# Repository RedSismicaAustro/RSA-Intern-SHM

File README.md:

# RSA Intern SHM

Repositorio para la **migración de proyectos electrónicos desde Altium Designer hacia KiCad 10** desarrollados para el sistema **RSA Structural Health Monitoring (SHM)**.

El propósito de este repositorio es preservar los diseños electrónicos existentes, reemplazar las bibliotecas propietarias utilizadas en Altium por bibliotecas locales compatibles con KiCad y establecer un flujo de trabajo estandarizado para el mantenimiento del hardware mediante herramientas de código abierto.

Como parte del proceso de migración, cada proyecto es revisado para verificar la integridad del esquemático y del PCB, actualizar las bibliotecas de símbolos y huellas, asociar modelos tridimensionales, asignar códigos **LCSC** a los componentes compatibles con **JLCPCB** y generar nuevamente todos los archivos necesarios para fabricación y ensamblaje automático.

La documentación específica de cada tarjeta se encuentra en la carpeta **Docs**, mientras que las bibliotecas compartidas se almacenan dentro de **KiCad/libs**, permitiendo reutilizar componentes entre diferentes proyectos y garantizando que cualquier desarrollador pueda abrir los diseños sin depender de configuraciones locales.

---

# Objetivos

El proceso de migración busca establecer una metodología uniforme para todos los proyectos electrónicos del sistema SHM. Los principales objetivos del repositorio son:

- Migrar los diseños electrónicos desde Altium Designer hacia KiCad 10.
- Eliminar dependencias de bibliotecas propietarias.
- Centralizar símbolos, footprints y modelos 3D en bibliotecas locales.
- Mantener todos los proyectos bajo control de versiones mediante Git.
- Preparar los diseños para fabricación y ensamblaje mediante JLCPCB.
- Documentar el proceso de migración para facilitar futuras modificaciones y revisiones.

---

# Estructura del repositorio

El repositorio se organiza de manera que cada proyecto conserve su propia documentación, mientras que las bibliotecas compartidas permanecen centralizadas para facilitar su reutilización.

```text
RSA-Intern-SHM/
│
├── Docs/
│   ├── Nodo/
│   │   └── README.md
│   ├── Concentrador/
│   │   └── README.md
│   ├── Concentrador2/
│   │   └── README.md
│   └── ...
│
├── KiCad/
│   ├── libs/
│   │   ├── RSA.kicad_sym
│   │   ├── RSA.pretty/
│   │   ├── LibExt.pretty/
│   │   └── packages3d/
│   │
│   └── projects/
│       ├── Nodo/
│       ├── Concentrador/
│       ├── Concentrador2/
│       └── ...
│
├── Firmware/
│
├── Production/
│
└── README.md
```

La carpeta `KiCad/projects` contiene los proyectos electrónicos migrados, mientras que `KiCad/libs` almacena todas las bibliotecas compartidas utilizadas por los diferentes diseños. Esta organización evita duplicar componentes y simplifica el mantenimiento de las bibliotecas a medida que nuevos proyectos son incorporados al repositorio.

---

# Herramientas utilizadas

La migración y mantenimiento de los proyectos se realiza utilizando herramientas de código abierto y utilidades complementarias para automatizar la generación de bibliotecas y archivos de fabricación.

| Herramienta | Descripción |
|-------------|-------------|
| KiCad 10 | Diseño y edición de esquemáticos y PCB |
| Python 3 | Automatización de herramientas auxiliares |
| Git | Control de versiones |
| JLC2KiCadLib | Descarga automática de símbolos, footprints y modelos 3D |
| Fabrication Toolkit | Generación de BOM, CPL, Gerbers y NC Drill |
| JLCPCB | Fabricación y ensamblaje PCBA |

---

# Flujo de migración

Todos los proyectos contenidos en este repositorio siguen un procedimiento de migración común con el objetivo de mantener una estructura uniforme y facilitar el mantenimiento futuro.

El proceso comienza con la importación del proyecto desde Altium Designer hacia KiCad. Posteriormente se realiza una revisión completa del esquemático y del PCB para verificar que las conexiones eléctricas, las referencias de componentes y las reglas de diseño hayan sido importadas correctamente.

Una vez validado el diseño, se sustituyen las bibliotecas originales por bibliotecas locales compatibles con KiCad. Cada símbolo queda asociado con su respectiva huella y, cuando está disponible, con su modelo tridimensional.

Posteriormente se revisan los componentes para identificar aquellos compatibles con el servicio PCBA de JLCPCB. A estos componentes se les asigna su correspondiente código LCSC, permitiendo automatizar la generación de la lista de materiales y del archivo de posicionamiento durante el proceso de fabricación.

Finalmente se ejecutan las verificaciones ERC y DRC, se generan los archivos Gerber, NC Drill, BOM y CPL mediante Fabrication Toolkit y se valida la documentación obtenida utilizando el visor de JLCPCB.

---

# Organización de bibliotecas

Uno de los principales objetivos de la migración consiste en eliminar la dependencia de bibliotecas instaladas globalmente. Para ello, todos los símbolos, footprints y modelos tridimensionales utilizados por los proyectos se almacenan dentro del repositorio.

Las bibliotecas principales utilizadas son:

- RSA.kicad_sym
- RSA.pretty
- LibExt.pretty

Los modelos tridimensionales asociados a cada componente se almacenan dentro de la carpeta `packages3d`, mientras que los componentes descargados automáticamente desde JLCPCB se incorporan a las bibliotecas locales mediante **JLC2KiCadLib**.

Esta organización garantiza que cualquier proyecto pueda abrirse correctamente después de clonar el repositorio, independientemente del equipo utilizado.

---

# Proyectos

Actualmente el repositorio contiene varias tarjetas electrónicas migradas desde Altium Designer hacia KiCad 10.

| Proyecto | Descripción |
|-----------|-------------|
| Nodo | Nodo de adquisición de datos del sistema SHM. |
| Concentrador | Tarjeta concentradora de comunicaciones. |
| Concentrador2 | Segunda revisión del concentrador con mejoras de hardware. |

Cada proyecto dispone de un archivo `README.md` independiente dentro de la carpeta `Docs`, donde se documenta el procedimiento de migración, la configuración de bibliotecas, la lista de componentes, los códigos LCSC y el proceso de generación de archivos de fabricación.

---

# Preparación para fabricación

Todos los diseños fueron preparados para ser fabricados utilizando el servicio **JLCPCB PCBA**. Los componentes compatibles emplean códigos **LCSC**, permitiendo automatizar la generación de la lista de materiales y el posicionamiento de componentes durante el ensamblaje.

Antes de generar los archivos de producción se revisan las propiedades de cada componente para configurar correctamente las opciones **Exclude from BOM** y **Exclude from Board**, evitando que conectores, elementos mecánicos o componentes de montaje manual sean incluidos en los archivos de ensamblaje.

La documentación de fabricación generada para cada proyecto incluye:

- Gerber
- NC Drill
- Bill of Materials (BOM)
- Component Placement List (CPL)

Estos archivos pueden almacenarse dentro de la carpeta `Production` correspondiente a cada diseño para facilitar futuras órdenes de fabricación.

---

# Buenas prácticas

Para mantener la consistencia del repositorio se recomienda utilizar exclusivamente las bibliotecas locales almacenadas en `KiCad/libs` y evitar referencias a bibliotecas instaladas globalmente. Asimismo, cualquier componente nuevo debe incorporar su correspondiente símbolo, huella y modelo tridimensional antes de ser utilizado en un proyecto.

Se recomienda ejecutar las verificaciones ERC y DRC antes de cada liberación, mantener actualizados los códigos LCSC de los componentes compatibles con JLCPCB y validar los archivos Gerber, BOM y CPL utilizando el visor web del fabricante antes de confirmar una orden de producción.

Toda modificación realizada sobre un proyecto o una biblioteca debe registrarse mediante Git para conservar el historial de cambios y facilitar la colaboración entre los diferentes integrantes del equipo.

---

# Documentación

La documentación específica de cada tarjeta se encuentra disponible dentro de la carpeta `Docs`.

- `Docs/Nodo/README.md`
- `Docs/Concentrador/README.md`
- `Docs/Concentrador2/README.md`

Cada documento describe detalladamente el proceso de migración, los componentes utilizados, la configuración de bibliotecas, la asignación de códigos LCSC y la generación de los archivos de fabricación correspondientes.

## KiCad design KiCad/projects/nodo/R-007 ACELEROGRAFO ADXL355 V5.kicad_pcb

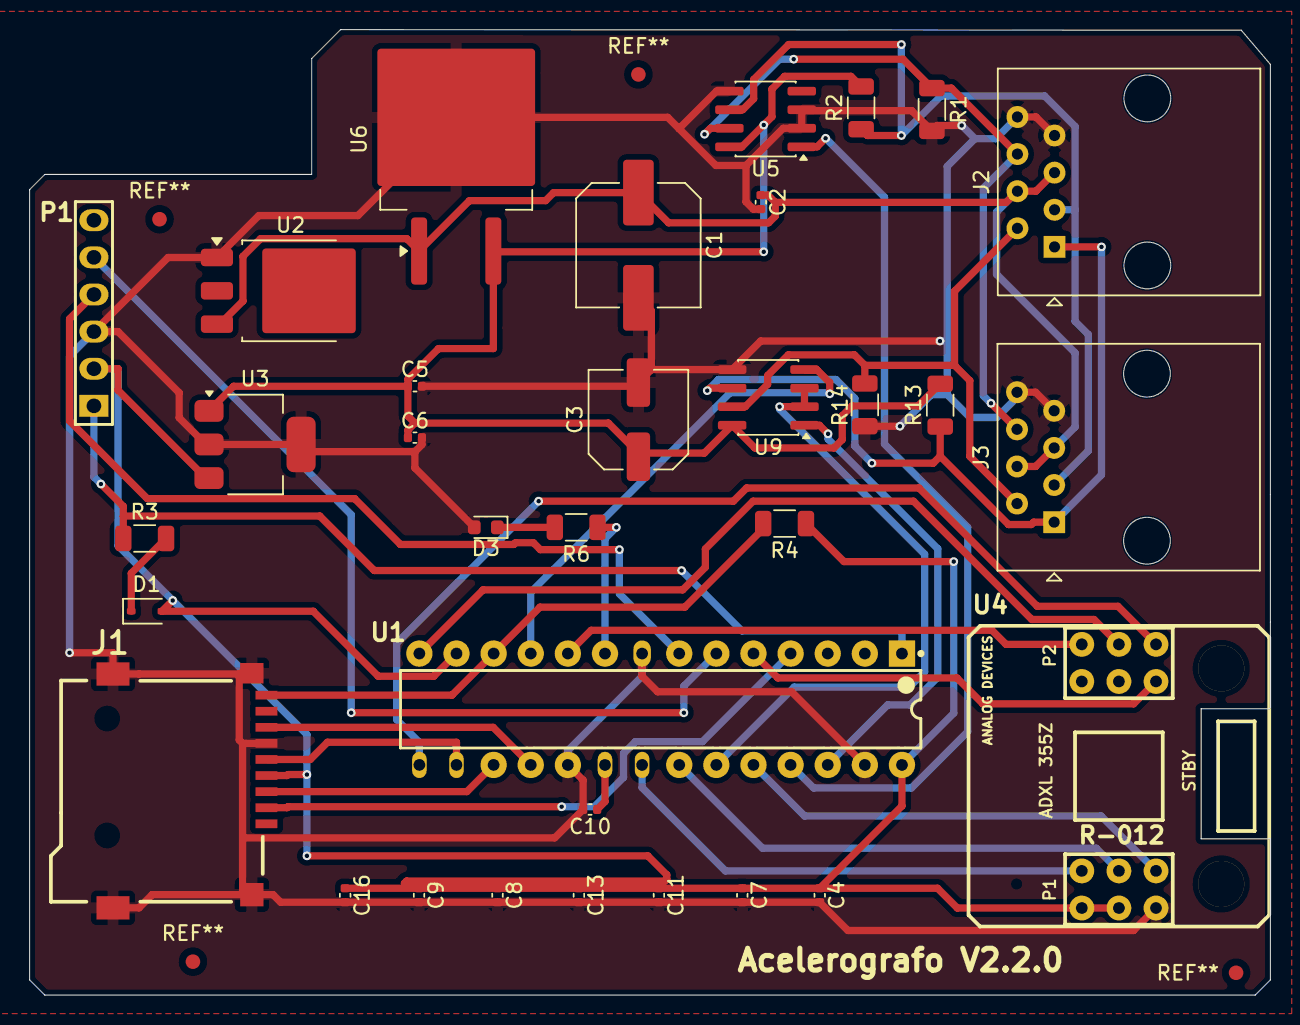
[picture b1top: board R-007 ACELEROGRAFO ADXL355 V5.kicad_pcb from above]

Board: 2 copper layers, 84.9 x 66.1 mm, 33 parts (0 on the bottom side), 31 nets.

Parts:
C1: Cap; C_Elec_8x10.2
C2, C4, C5, C6, C7, C8, C9, C10, C11, C13, C16: Cap; C_0402_1005Metric
C3: Cap; C_Elec_6.3x7.7
D1: 1N4148WS; D_SOD-323
D3: LED3; LED_0603_1608Metric
J1: ${ALTIUM_VALUE}${VALUEAUX}; microSD
J2, J3: 54602-908LF; RJ45_Amphenol_54602-x08_Horizontal
P1: Grabador; HDR1X6
R1, R2, R3, R4, R6, R13, R14: Res1; R_1206_3216Metric
U1: DSPIC33EP256MC202-I/SP; MCHP-SPDIP-SP28
U2: LM1117DT-5.0NOPB; TO-252-3_TabPin2
U3: LD33V; SOT-223-3_TabPin2
U4: ADXL355Z
U5, U9: MAX485; SOIC-8_3.9x4.9mm_P1.27mm
U6: LM7805_TO220; TO-263-2

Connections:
5V: C3.1, C5.1, C6.1, R2.2, R13.2, U3.1 (IN), U5.8, U6.3 (VO), U9.8
A: J2.1, J3.1, R13.1, U9.6
ADXL_DRDY: U1.24 (RPI45/PWM2L/CTPLS/RB13), U4.3 (DRDY)
ADXL_INT1: U1.21 (TDO/RP42/PWM3H/RB10), U4.1 (INT1)
ADXL_INT2: U1.22 (TDI/RP43/PWM3L/RB11), U4.2 (INT2)
B: J2.2, J3.2, R14.1, U9.7
ConSD: J1.9 (SH), R4.2, U1.12 (CVREF2O/RP20/T1CK/RA4)
DSPIC_RX: U1.26 (RPI47/PWM1L/T5CK/RB15), U9.1
DSPIC_TX: U1.11 (FLT32/RP36/RB4), U9.4
FUENTE_12V: C1.1, C2.1, J2.4, J2.5, J3.4, J3.5, U2.3 (INPUT), U6.1 (VI)
GND: C1.2, C2.2, C3.2, C4.2, C5.2, C6.2, C7.2, C8.2, C9.2, C10.2, C11.2, C13.2, C16.2, D3.2 (K), J1.6 (GND), J1.10 (CD), J2.7, J2.8, J3.7, J3.8, P1.3, R1.2, R14.2, U1.8 (VSS), U1.19 (VSS), U1.27 (AVSS), U2.1 (GND), U3.2 (GND), U4.6 (GND), U5.2, U5.3, U5.5, U6.2 (GND), U9.5
INT_SINC: U1.25 (RPI46/PWM1H/T3CK/RB14), U5.1
MAX485_MS: U1.23 (RPI44/PWM2H/RB12), U9.2, U9.3
MCLR: P1.1, R3.1, U1.1 (~MCLR)
unnamed: D1.1 (K), R3.2
unnamed: D3.1 (A), R6.2
unnamed: C10.1, U1.20 (VCAP)
SINC_A: J2.3, J3.3, R2.1, U5.6
SINC_B: J2.6, J3.6, R1.1, U5.7
SPI1_DSPIC_SS: J1.2 (CD/DAT3), U1.4 (PGED3/VREF-/AN2/C2IN1-/~SS1/RPI32/CTED2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)
SPI1_MISO: J1.7 (DAT0), U1.18 (TMS/ASDA1/SDI1/RP41/RB9)
SPI1_MOSI: J1.3 (CMD), U1.17 (TCK/CVREF1O/ASCL1/SDO1/RP40/T4CK/RB8)
SPI1_SCK: J1.5 (CLK), U1.16 (SCK1/RP39/INT0/RB7)
SPI2_ADXL355Z_CS: U1.10 (OSC2/CLKO/RA3), U4.7 (CS/SCL)
SPI2_MISO: U1.5 (PGEC3/VREF+/AN3/OA1OUT/RPI33/CTED1/RB1), U4.12 (MISO/SDA)
SPI2_MOSI: U1.15 (PGEC2/ASCL2/RP38/RB6), U4.9 (MOSI/SDA)
SPI2_SCK: U1.14 (PGED2/ASDA2/RP37/RB5), U4.8 (SCLK/GND)
TEST1: R6.1, U1.9 (OSC1/CLKI/RA2)
VCC: C4.1, C7.1, C8.1, C9.1, C11.1, C13.1, C16.1, D1.2 (A), J1.4 (VDD), P1.2, R4.1, U1.13 (VDD), U1.28 (AVDD), U3.3 (OUT), U4.4 (VDDIO), U4.5 (VDD)
_PGEC1: P1.5, U1.6 (PGEC1/AN4/C1IN1+/RPI34/RB2)
_PGED1: P1.4, U1.7 (PGED1/AN5/C1IN1-/RP35/RB3)

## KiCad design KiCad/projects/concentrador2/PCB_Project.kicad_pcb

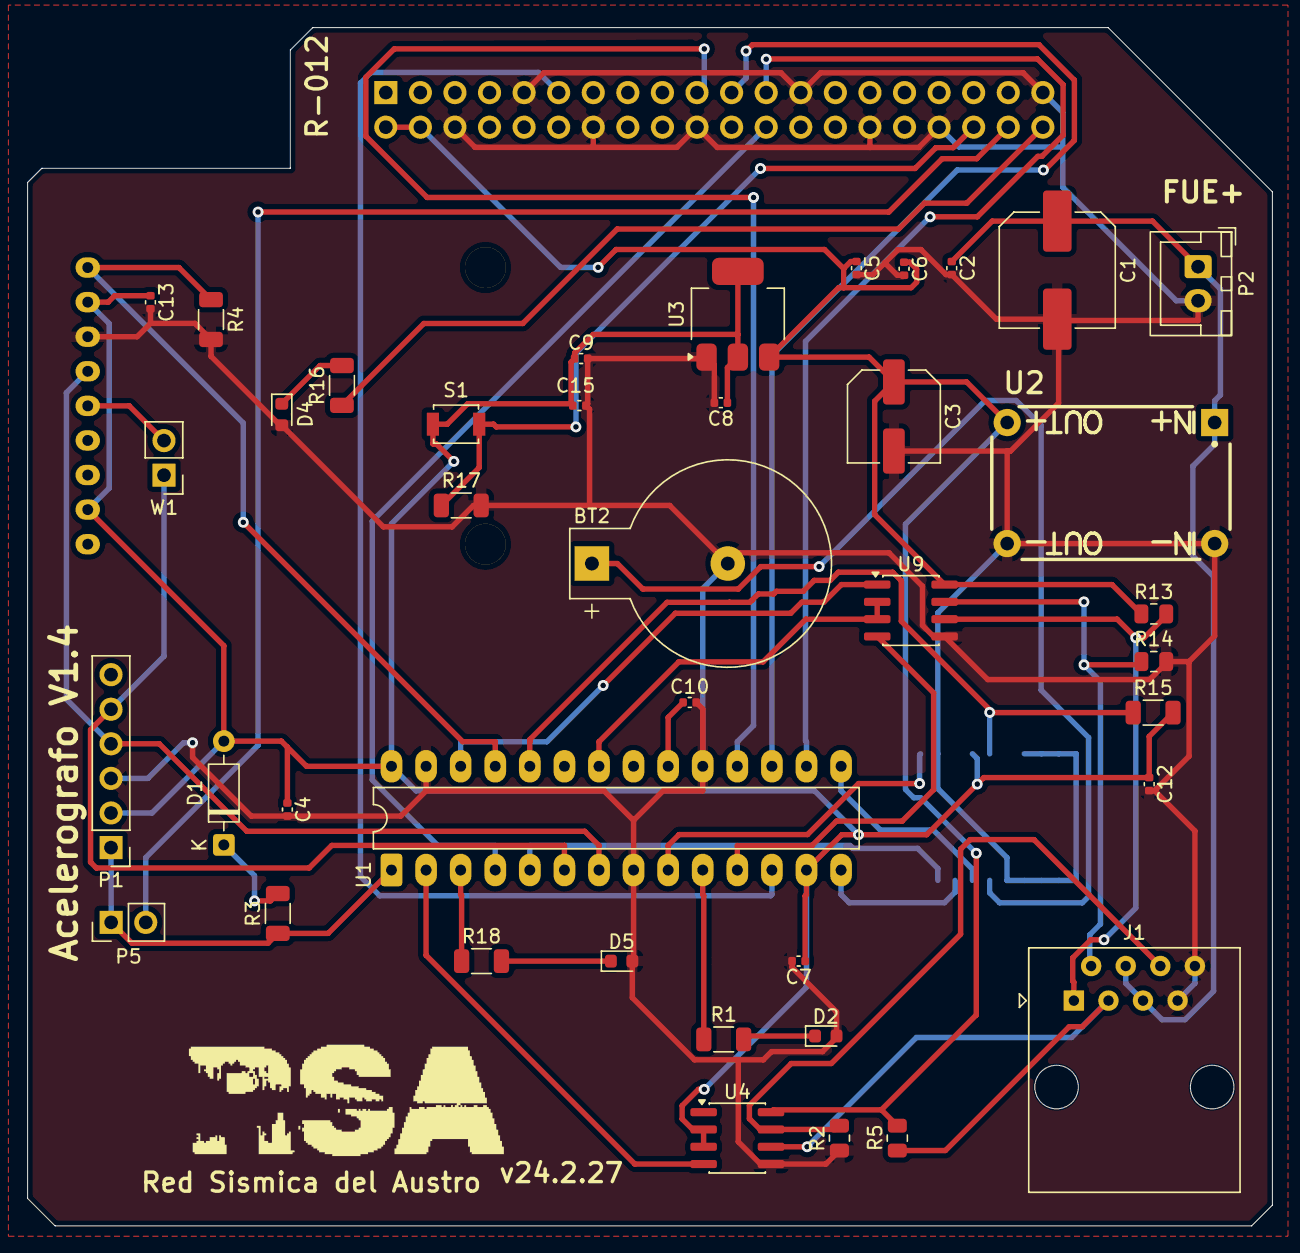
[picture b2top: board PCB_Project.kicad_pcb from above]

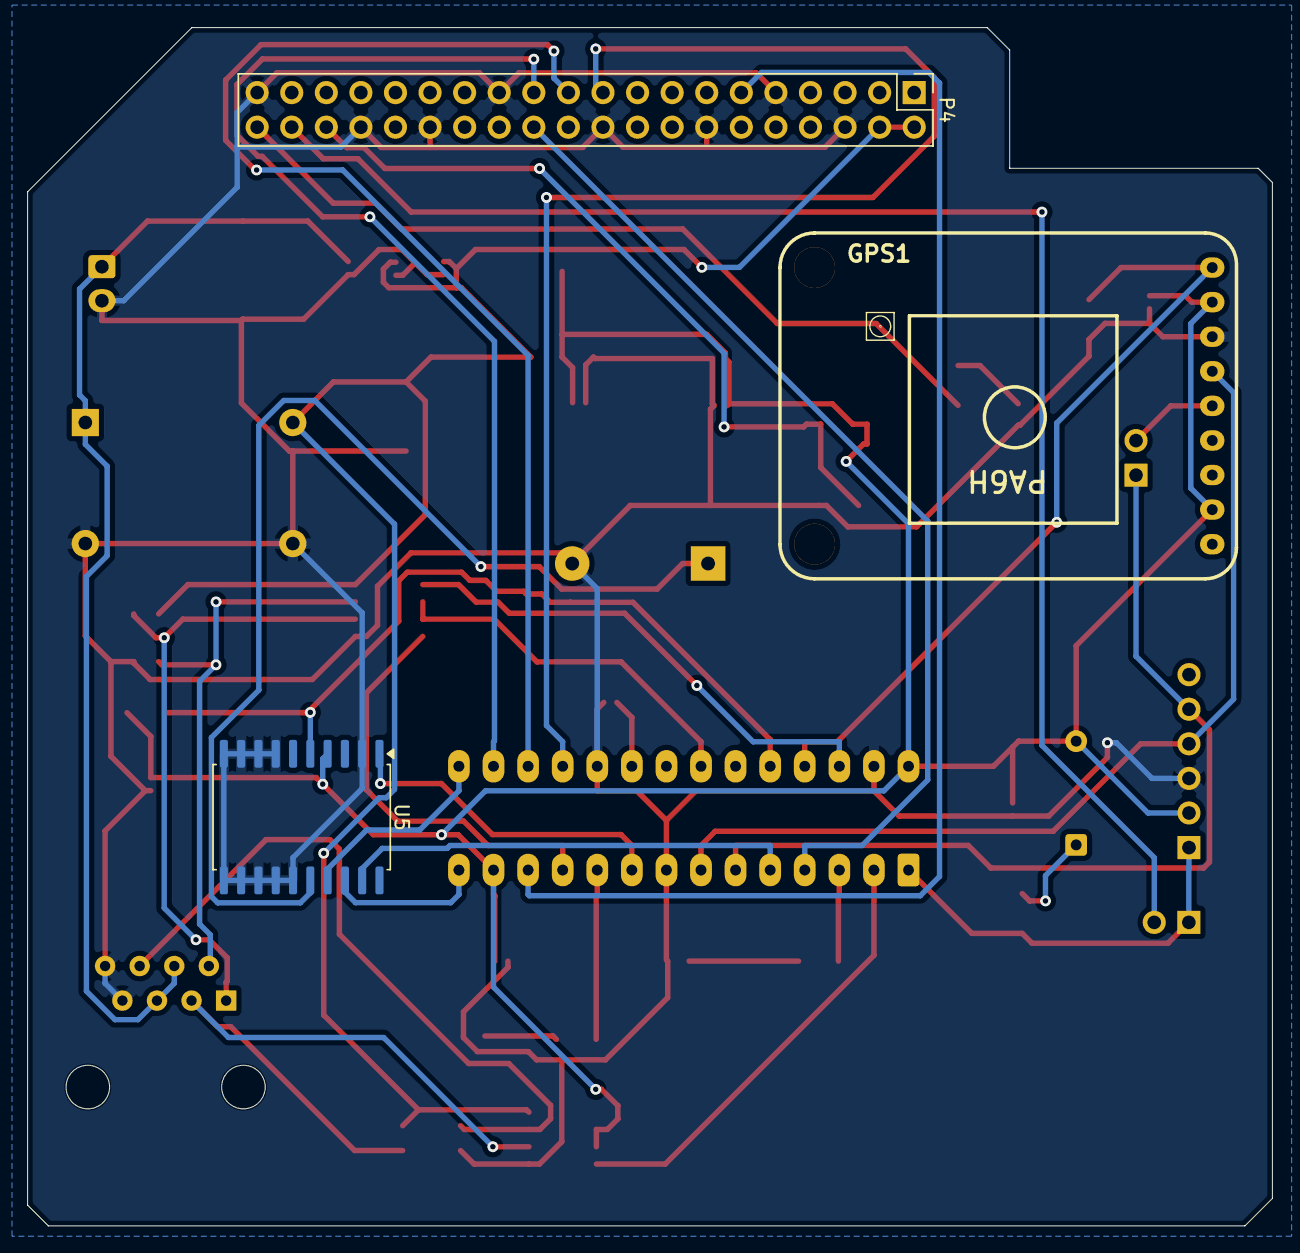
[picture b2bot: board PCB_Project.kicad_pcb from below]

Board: 2 copper layers, 91.4 x 88.0 mm, 43 parts (3 on the bottom side), 38 nets.

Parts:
BT2: Battery; BatteryHolder_Keystone_500
C1: 470uF; C_Elec_8x10.2
C2, C4, C5, C7, C8: 100nF; C_0402_1005Metric
C3: 220uF; C_Elec_6.3x7.7
C6, C9: 10nF; C_0402_1005Metric
C10, C12, C13, C15: Cap; C_0402_1005Metric
D1: 1N914; D_DO-35_SOD27_P7.62mm_Horizontal
D2, D4, D5: LED_white; LED_0603_1608Metric
GPS1: GPS_BREAKOUT_V3
J1: 54602-908LF; RJ45_Amphenol_54602-x08_Horizontal
P1: Grabador; PinHeader_1x06_P2.54mm_Vertical
P2: Entrada fuente externa; JST_XH_B2B-XH-A_1x02_P2.50mm_Vertical
P4: Header 20X2; PinHeader_2x20_P2.54mm_Vertical
P5: Header 2; PinHeader_1x02_P2.54mm_Vertical
R1, R3, R4, R16, R17, R18: Res1; R_1206_3216Metric
R2, R5, R14: Res1; R_0805_2012Metric
R13: 3K3; R_0805_2012Metric
R15: 10k; R_1206_3216Metric
S1: SW-PB; SW_SPST_B3U-1000P
U1: DSPIC33EP256MC202-I/SP; DIP-28_W7.62mm_LongPads
U2: STEP_DOWN_CONVERTER
U3: LD33V; SOT-223-3_TabPin2
U4, U9: MAX485; SOIC-8_3.9x4.9mm_P1.27mm
U5: DS3234S#; SOIC-20W_7.5x12.8mm_P1.27mm
W1: Jumper; PinHeader_1x02_P2.54mm_Vertical

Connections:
5V: C3.1, C5.1, C6.1, P4.2, P4.4, R5.2, R13.2, U2.3 (OUT+), U3.3 (VI), U4.8, U9.8
A: J1.1, R13.1, U9.6
B: J1.2, R14.1, U9.7
DS3231_SQW: R15.1, U1.24 (RPI45/PWM2L/CTPLS/RB13), U5.5 (INT/SQW)
DSPIC_RX: GPS1.4 (TXD), W1.2 (C2)
DSPIC_RX_1: U1.26 (RPI47/PWM1L/T5CK/RB15), U9.1
DSPIC_TX: GPS1.3 (RXD), P1.4, U1.7 (PGED1/AN5/C1IN1-/RP35/RB3)
DSPIC_TX_1: U1.11 (FLT32/RP36/RB4), U9.4
FUENTE_12V: C1.1, C2.1, J1.4, J1.5, P2.1, U2.1 (IN+)
GND: BT2.2 (-), C1.2, C2.2, C3.2, C4.2, C5.2, C6.2, C7.2, C8.2, C9.2, C10.2, C12.2, C13.2, C15.2, D2.2 (K), D4.2 (K), D5.2 (K), GPS1.2 (GND), J1.7, J1.8, P1.3, P2.2, P4.6, P4.9, P4.14, P4.20, P4.25, P4.30, P4.34, P4.39, R2.2, R4.2, R14.2, R17.2, U1.8 (VSS), U1.19 (VSS), U1.27 (AVSS), U2.2 (IN-), U2.4 (OUT-), U3.1 (GND), U4.5, U5.2 (NC), U5.7 (NC), U5.8 (NC), U5.9 (NC), U5.10 (NC), U5.11 (NC), U5.12 (NC), U5.13 (NC), U5.14 (NC), U5.15 (GND), U9.5
GPS_1PPS: GPS1.0 (1PPS), R4.1, U1.25 (RPI46/PWM1H/T3CK/RB14)
INT_SINC_1: U1.2 (AN0/OA2OUT/RA0), U4.4
INT_SINC_2: R1.1, U1.10 (OSC2/CLKO/RA3)
LED_DSPIC: R18.1, U1.3 (AN1/C2IN1+/RA1)
LED_RPI: P4.40, R16.1
MAX485_MS: U1.22 (TDI/RP43/PWM3L/RB11), U9.2, U9.3
MCLR: P1.1, P5.1, R3.1, U1.1 (~MCLR)
unnamed: D1.1 (K), R3.2
unnamed: D2.1 (A), R1.2
unnamed: D4.1 (A), R16.2
unnamed: D5.1 (A), R18.2
unnamed: C10.1, U1.20 (VCAP)
NetBT1_0: BT2.1 (+), U5.16 (VBAT)
ONOFF: P4.36, R17.1, S1.2
RESET: P4.38, P5.2
RPI_INT1: P4.11, U1.12 (CVREF2O/RP20/T1CK/RA4)
SINC_A: J1.3, R5.1, U4.6
SINC_B: J1.6, R2.1, U4.7
SPI1_DSPIC_SS: P4.24, U1.4 (PGED3/VREF-/AN2/C2IN1-/~SS1/RPI32/CTED2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)
SPI1_MISO: P4.21, U1.17 (TCK/CVREF1O/ASCL1/SDO1/RP40/T4CK/RB8)
SPI1_MOSI: P4.19, U1.18 (TMS/ASDA1/SDI1/RP41/RB9)
SPI1_SCK: P4.23, U1.16 (SCK1/RP39/INT0/RB7)
SPI2_DS3234_CS: U1.9 (OSC1/CLKI/RA2), U5.1 (CS)
SPI2_MISO: U1.5 (PGEC3/VREF+/AN3/OA1OUT/RPI33/CTED1/RB1), U5.19 (MISO)
SPI2_MOSI: U1.15 (PGEC2/ASCL2/RP38/RB6), U5.17 (MOSI)
SPI2_SCK: U1.14 (PGED2/ASDA2/RP37/RB5), U5.18 (SCLK)
VCC: C4.1, C7.1, C8.1, C9.1, C12.1, C13.1, C15.1, D1.2 (A), GPS1.1 (VIN), GPS1.7 (EN), P1.2, R15.2, S1.1, U1.13 (VDD), U1.28 (AVDD), U3.2 (VO), U4.2, U4.3, U5.4 (VCC)
_DSPIC_RX: P1.5, U1.6 (PGEC1/AN4/C1IN1+/RPI34/RB2), W1.1 (C1)

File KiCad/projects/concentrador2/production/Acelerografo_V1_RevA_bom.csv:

Designator,Footprint,Quantity,Value,LCSC Part #
C1,C_Elec_8x10.2,1,470uF,C2858857
C10,0402,1,Cap,C29266
"C12, C13, C15",0402,3,Cap,C1525
"C2, C4, C5, C7, C8",0402,5,100nF,C1525
C3,C_Elec_6.3x7.7,1,220uF,C970695
"C6, C9",0402,2,10nF,C15195
"D2, D4, D5",0603,3,LED_white,C2290
"R1, R16, R18",1206,3,Res1,C4410
R13,0805,1,3K3,C26010
"R14, R2, R5",0805,3,Res1,C26010
R15,1206,1,10k,C17902
R17,1206,1,Res1,C17902
R3,1206,1,Res1,C17936
R4,1206,1,Res1,C17900
S1,SW_SPST_B3U-1000P,1,SW-PB,C720477
U3,SOT-223-3_TabPin2,1,LD33V,C35879
"U4, U9",SOIC-8_3.9x4.9mm_P1.27mm,2,MAX485,C481667
U5,SOIC-20W_7.5x12.8mm_P1.27mm,1,DS3234S#,C2651511

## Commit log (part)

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2026-04-20 init: Inicio del proyecto - Se agregaron los archivos de Altium del concentrador - Se agrego el archivo gitignore
2026-04-21 Agrega estructura base KiCad
2026-04-22 Importación inicial del proyecto concentrador desde Altium a KiCad
2026-04-24 docs: Se agregaron los archivos de Altium del nodo
2026-05-06 Migracion a SMD
2026-05-06 Ignora carpetas de historial local
2026-05-11 Fase 3
2026-06-03 Fase 4 - Asignación para PCBA
2026-06-04 Fase 4 - 2
2026-06-11 Archivos Gerber

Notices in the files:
parts and their libraries:
COPYRIGHT: Copyright (C) 2018 Accelerated Designs. All rights reserved
